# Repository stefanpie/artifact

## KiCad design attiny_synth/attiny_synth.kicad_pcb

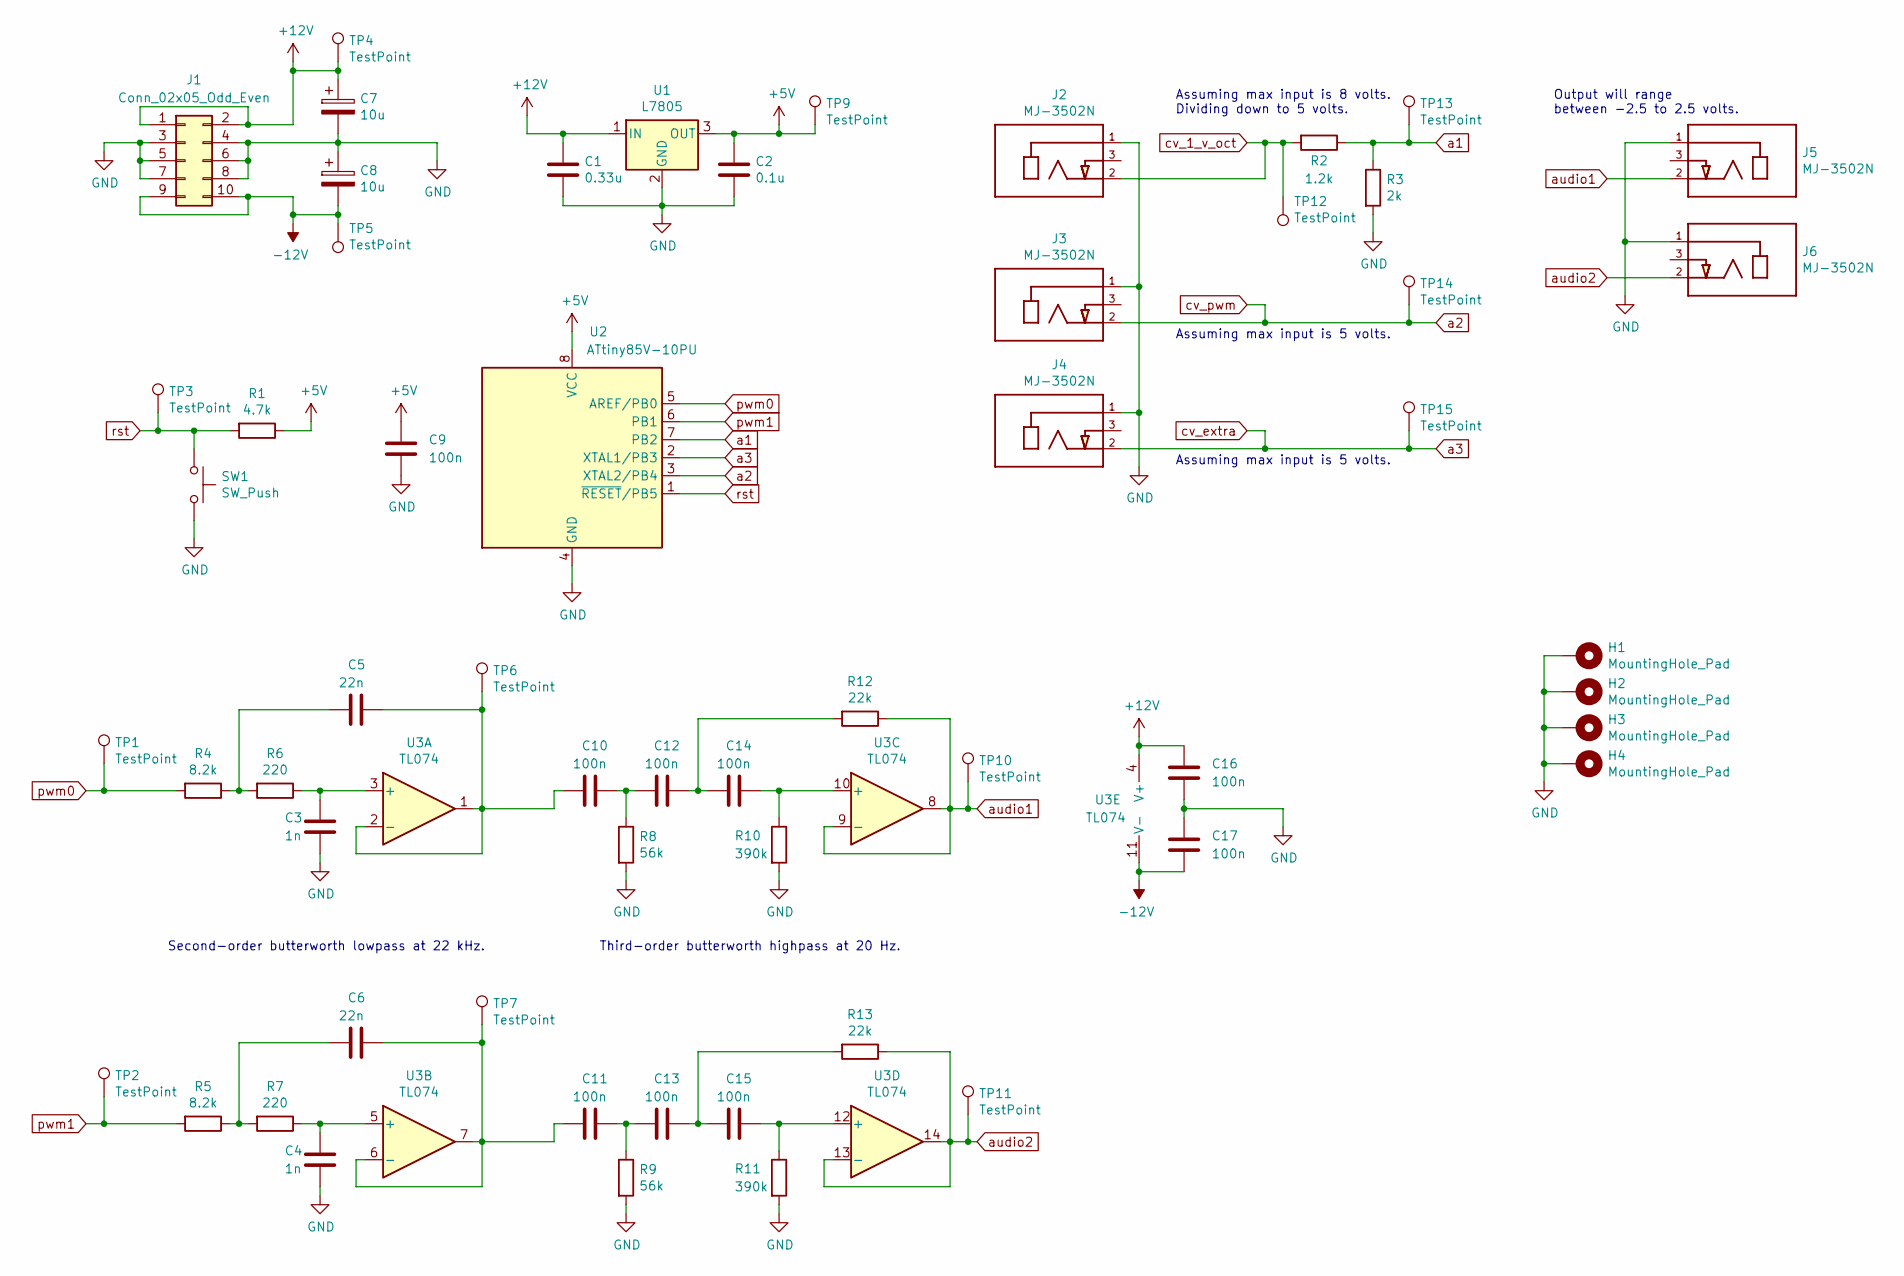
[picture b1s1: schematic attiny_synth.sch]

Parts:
C1: 0.33u; C_Disc_D7.0mm_W2.5mm_P5.00mm
C2: 0.1u; C_Disc_D7.0mm_W2.5mm_P5.00mm
C3, C4: 1n; C_Disc_D7.0mm_W2.5mm_P5.00mm
C5, C6: 22n; C_Disc_D7.0mm_W2.5mm_P5.00mm
C7, C8: 10u; C_Disc_D7.0mm_W2.5mm_P5.00mm
C9, C10, C11, C12, C13, C14, C15, C16, C17: 100n; C_Disc_D7.0mm_W2.5mm_P5.00mm
H1, H2, H3, H4: MountingHole_Pad; MountingHole_4.3mm_M4_Pad_Via
J1: Conn_02x05_Odd_Even; PinHeader_2x05_P2.54mm_Vertical
J2, J3, J4, J5, J6: MJ-3502N; CUI_MJ-3502N
R1: 4.7k; R_Axial_DIN0207_L6.3mm_D2.5mm_P10.16mm_Horizontal
R2: 1.2k; R_Axial_DIN0207_L6.3mm_D2.5mm_P10.16mm_Horizontal
R3: 2k; R_Axial_DIN0207_L6.3mm_D2.5mm_P10.16mm_Horizontal
R4, R5: 8.2k; R_Axial_DIN0207_L6.3mm_D2.5mm_P10.16mm_Horizontal
R6, R7: 220; R_Axial_DIN0207_L6.3mm_D2.5mm_P10.16mm_Horizontal
R8, R9: 56k; R_Axial_DIN0207_L6.3mm_D2.5mm_P10.16mm_Horizontal
R10, R11: 390k; R_Axial_DIN0207_L6.3mm_D2.5mm_P10.16mm_Horizontal
R12, R13: 22k; R_Axial_DIN0207_L6.3mm_D2.5mm_P10.16mm_Horizontal
SW1: SW_Push; SW_PUSH_6mm
TP1, TP2, TP3, TP4, TP5, TP6, TP7, TP9, TP10, TP11, TP12, TP13, TP14, TP15: TestPoint; TestPoint_Pad_2.5x2.5mm
U1: L7805; TO-220-3_Horizontal_TabDown
U2: ATtiny85V-10PU; DIP-8_W7.62mm
U3: TL074; DIP-16_W7.62mm

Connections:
+5V: C2.1, C9.1, R1.1, TP9.1, U1.3 (OUT), U2.8 (VCC)
+12V: C1.1, C7.1, C16.1, J1.1, J1.2, TP4.1, U1.1 (IN), U3.4 (V+)
-12V: C8.2, C17.2, J1.9, J1.10, TP5.1, U3.11 (V-)
GND: C1.2, C2.2, C3.2, C4.2, C7.2, C8.1, C9.2, C16.2, C17.1, H1.1, H2.1, H3.1, H4.1, J1.3, J1.4, J1.5, J1.6, J1.7, J1.8, J2.1 (S), J3.1 (S), J4.1 (S), J5.1 (S), J6.1 (S), R3.2, R8.2, R9.2, R10.2, R11.2, SW1.2, U1.2 (GND), U2.4 (GND)
unnamed: C3.1, R6.1, U3.3 (+)
unnamed: C4.1, R7.1, U3.5 (+)
unnamed: C5.2, R4.1, R6.2
unnamed: C6.2, R5.1, R7.2
unnamed: C10.1, C12.2, R8.1
unnamed: C5.1, C10.2, TP6.1, U3.1, U3.2 (-)
unnamed: C11.1, C13.2, R9.1
unnamed: C6.1, C11.2, TP7.1, U3.6 (-), U3.7
unnamed: C12.1, C14.2, R12.2
unnamed: C13.1, C15.2, R13.2
unnamed: C14.1, R10.1, U3.10 (+)
unnamed: C15.1, R11.1, U3.12 (+)
a1: R2.1, R3.1, TP13.1, U2.7 (PB2)
a2: J3.2 (T), TP14.1, U2.3 (XTAL2/PB4)
a3: J4.2 (T), TP15.1, U2.2 (XTAL1/PB3)
audio1: J5.2 (T), R12.1, TP10.1, U3.8, U3.9 (-)
audio2: J6.2 (T), R13.1, TP11.1, U3.13 (-), U3.14
cv_1_v_oct: J2.2 (T), R2.2, TP12.1
pwm0: R4.2, TP1.1, U2.5 (AREF/PB0)
pwm1: R5.2, TP2.1, U2.6 (PB1)
rst: R1.2, SW1.1, TP3.1, U2.1 (~RESET~/PB5)

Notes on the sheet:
Assuming max input is 8 volts. Dividing down to 5 volts.
Assuming max input is 5 volts.
Output will range between -2.5 to 2.5 volts.
Second-order butterworth lowpass at 22 kHz.
Third-order butterworth highpass at 20 Hz.

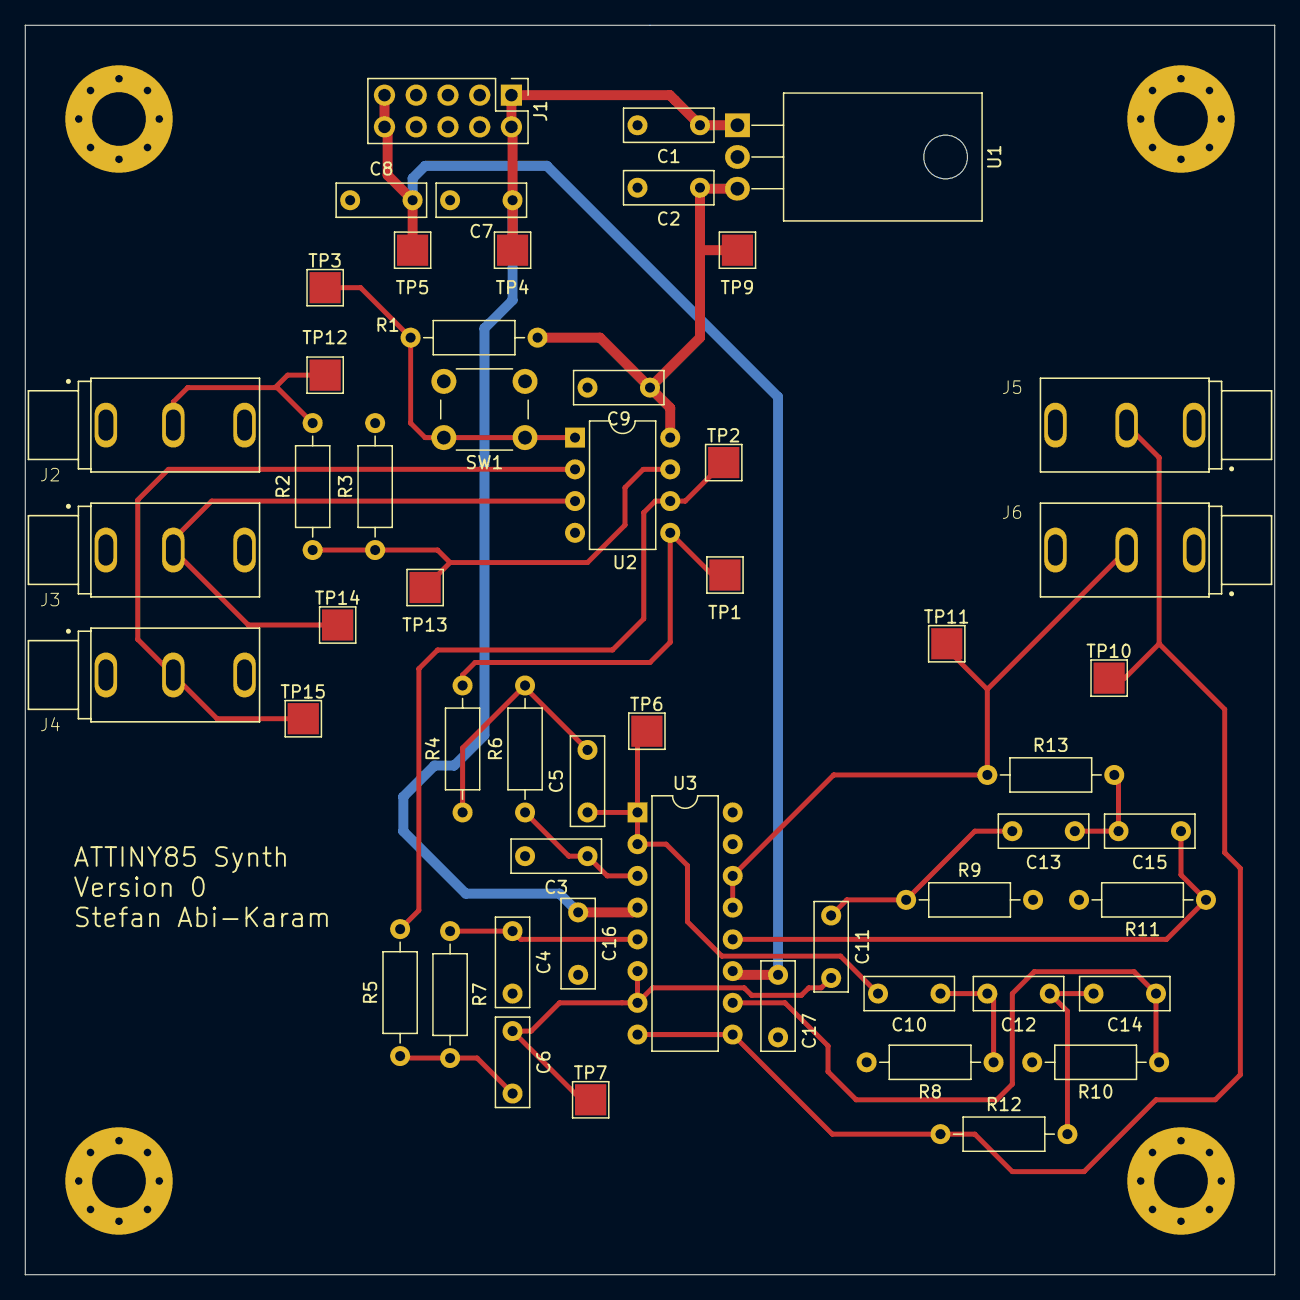
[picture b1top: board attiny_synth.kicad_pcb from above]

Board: 2 copper layers, 100.0 x 100.0 mm, 58 parts (0 on the bottom side), 25 nets.

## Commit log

2021-06-29 added initial files from old designs with attiny
